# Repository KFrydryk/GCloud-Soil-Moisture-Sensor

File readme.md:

# Google Cloud Soil Moisture Sensor

This is a home project and an exercise on using Cloud solutions in IoT. 

The project uses a generic soil moisture sensor and a photoresistor with ESP8266 and complementary devices (resistors, buttons, voltage regulator and some pin headers).

[*Results can be seen here!*](https://datastudio.google.com/reporting/f9fdeeb2-1fdc-4f80-99da-87816e4d7d12)

# How does it work?

The data is from the sensor is gathered as analog value and mapped to 0-100% range. ESP8266s analog in is rated for 0-1V only so the reading has to be transformed via a simple voltage divider.
Photoresistor value is mapped to binary values of 0 (dark) and 100 (light) as ESP8266 has only 1 analog input. To make it more consistent, the value is gathered form a variable voltage divider and reading routine sets the input pin value high before the actual reading process. It guarantees same voltage threshold for low/high exposition transitions despite the input hysteresis.
Data is filtered by a simple moving average filter and translated into JSON format, which can be sent using MQTT protocol to Google IoT service.
IoT routine sets off a google Cloud Function service to parse the JSON data and insert it into BigQuery database.
For graphical output Google Datastudio is used. Data is obtained using automated SQL query every hour or on users demand.

# PCB
PCB was designed in Autocad EAGLE, all of the necessary files should be updated in [Eagle_files folder](https://github.com/KFrydryk/GCloud-Soil-Moisture-Sensor/tree/master/Eagle_files)

# Schematic

# Board

# Photo

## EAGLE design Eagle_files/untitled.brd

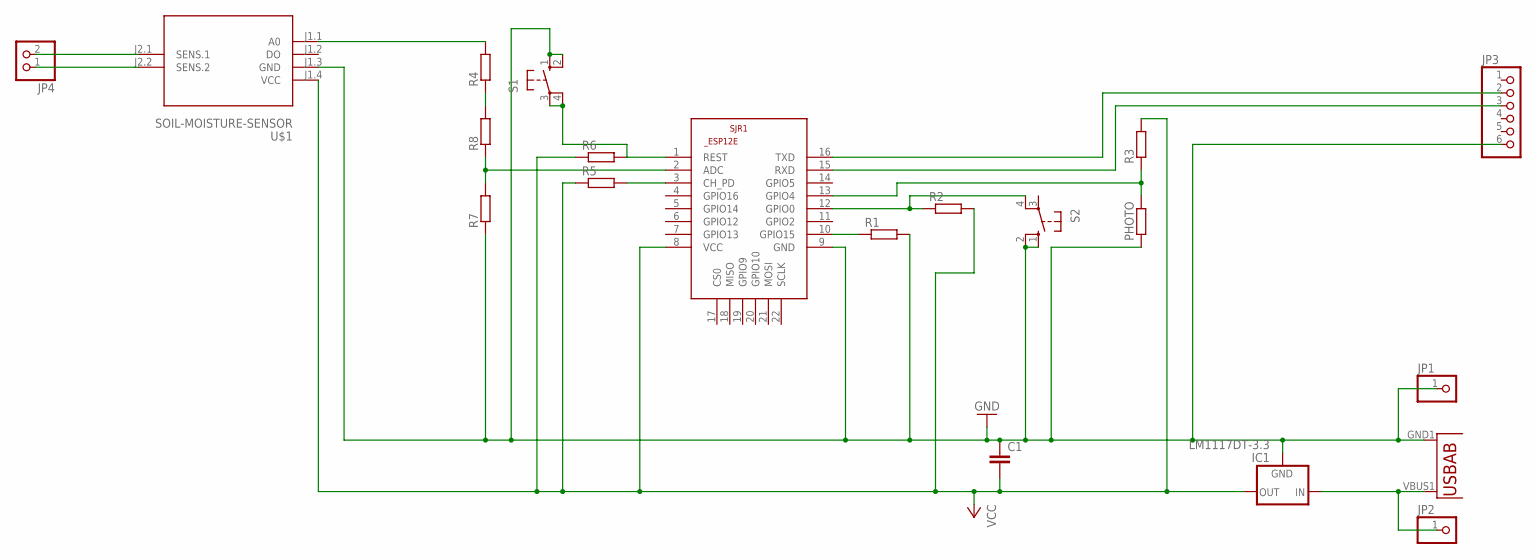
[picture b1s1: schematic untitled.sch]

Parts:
C1: C-EU050-025X075; C050-025X075
IC1: LM1117DT-3.3; TO252
JP1, JP2: PINHD-1X1; 1X01
JP3: PINHD-1X6; 1X06
JP4: PINHD-1X2; 1X02
PHOTO: R-EU_0204/5; 0204/5
R1, R2, R3, R4, R5, R6, R7, R8: R-EU_0207/10; 0207/10
S1, S2: 10-XX; B3F-10XX
SJR1: ESP8266-12EESP12E; ESP8266-ESP12E
U1: USB""; USB-MICRO-SMD
U$1: SOIL-MOISTURE-SENSOR

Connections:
GND: C1.1, IC1.1 (GND), JP1.1, JP3.6, PHOTO.1, R1.2, R7.1, S1.1 (S), S1.2 (S1), S2.1 (S), S2.2 (S1), SJR1.9 (GND), U1.GND1 (GND), U$1.J1.3 (GND)
unnamed: IC1.2 (IN), JP2.1, U1.VBUS1 (VBUS)
unnamed: R1.1, SJR1.10 (GPIO15)
unnamed: R2.1, S2.4 (P1), SJR1.12 (GPIO0)
unnamed: PHOTO.2, R3.1, SJR1.13 (GPIO4)
unnamed: JP3.3, SJR1.15 (RXD)
unnamed: JP3.2, SJR1.16 (TXD)
unnamed: R5.2, SJR1.3 (CH_PD)
unnamed: R7.2, R8.1, SJR1.2 (ADC)
unnamed: R4.1, R8.2
unnamed: R4.2, U$1.J1.1 (A0)
unnamed: R6.2, S1.3, S1.4 (P1), SJR1.1 (REST)
unnamed: JP4.2, U$1.J2.1 (SENS.1)
unnamed: JP4.1, U$1.J2.2 (SENS.2)
VCC: C1.2, IC1.3 (OUT), R2.2, R3.2, R5.1, R6.1, SJR1.8 (VCC), U$1.J1.4 (VCC)

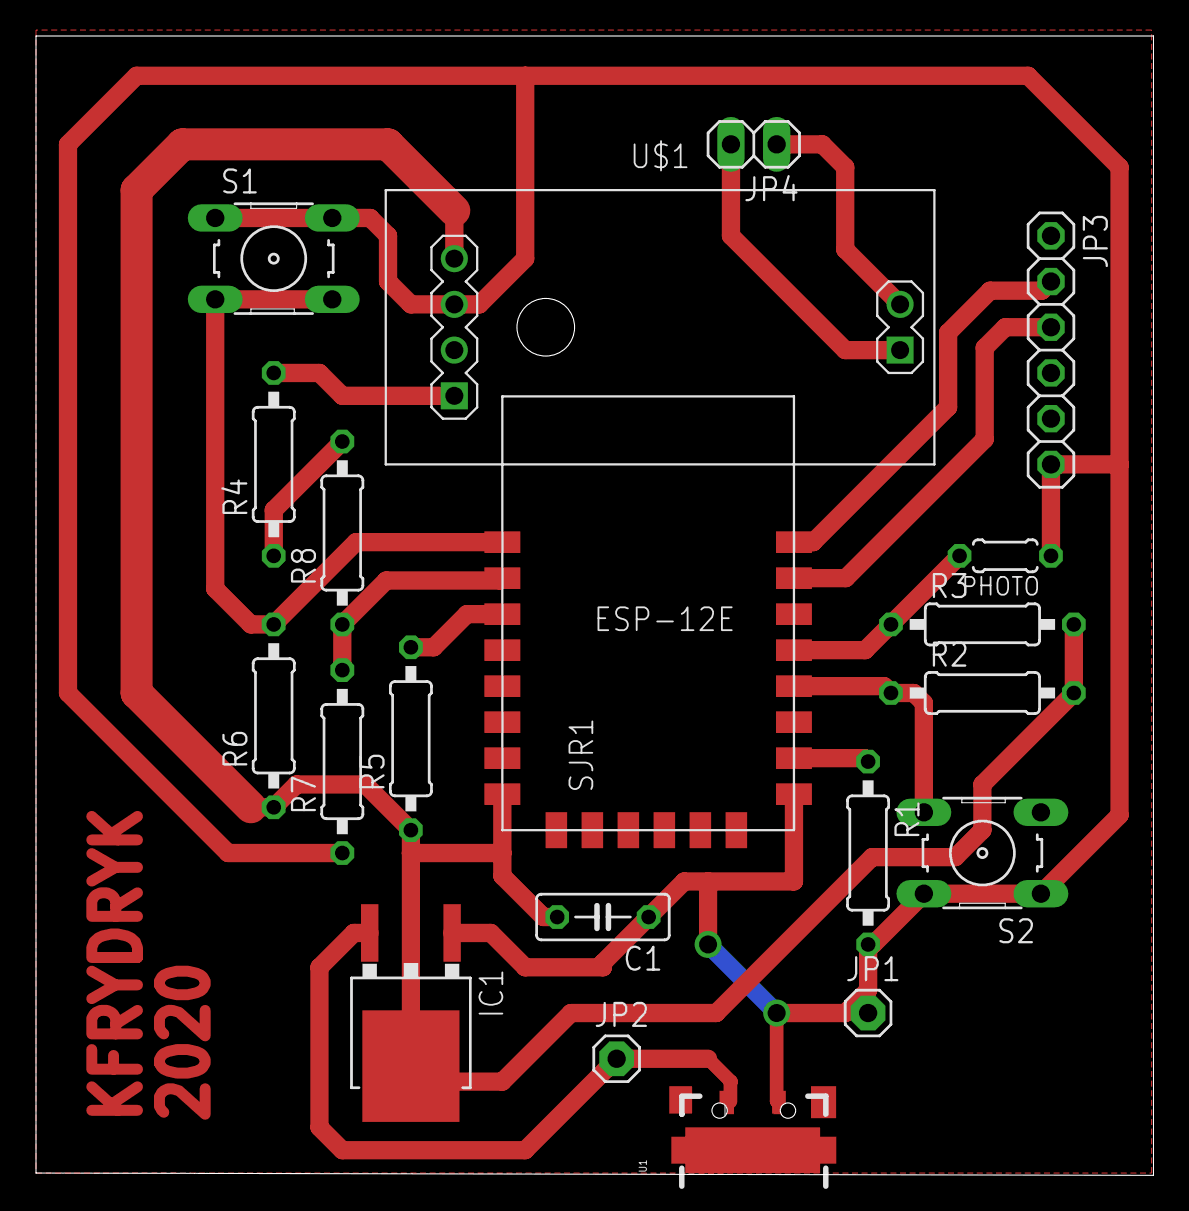
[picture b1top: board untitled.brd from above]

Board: 2 copper layers, 62.1 x 63.3 mm, 20 parts (0 on the bottom side), 15 nets.

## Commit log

2020-05-04 added Readme and schematics
2020-05-04 fixed readme.md
2020-05-04 added actual .ino file

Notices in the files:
parts and their libraries:
diy-modules: Released under the Creative Commons Attribution 4.0 International License: http://creativecommons.org/licenses/by/4.0
